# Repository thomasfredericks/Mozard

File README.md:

# Mozard

Mozard is a miniature, open-source digital synthesizer based on the Mozzi audio library and an Arduino Nano (ATmega328p) board.

[Video demonstration](https://youtu.be/wlpf26ogcaQ)

Features :

- 12 capacitive touch pads (one full octave)
- 6 different sound algorithms
- MIDI input support
- Octave control via potentiometer
- Volume control via potentiometer
- Built-in arpeggiator
- Decay and arpeggiator speed control

## Usage

The Mozard changes behavior when the arpeggiator is deactivated or activated. When in arpeggiator mode, the LED on the Arduino blinks in sync with the arpeggiator interval.

## Hardware

The circuit and Bill Of Materials can be found in the extras/circuit folder.

## Source code

1) Download the library source code [here](https://github.com/thomasfredericks/Mozard/archive/refs/heads/master.zip).

2) Extract into your Arduino libraries folder. It should look something like this:

3) Open Arduino.

4) Find the latest example:

5) Configure Arduino for the right microcontroller i.e. "Arduino Nano":

7) Configure Arduino for the right Bootloader i.e. "ATmega328 (Old Bootloader)"  if you followed a Mozard workshop or bought a clone:

8) Compile and transfer.

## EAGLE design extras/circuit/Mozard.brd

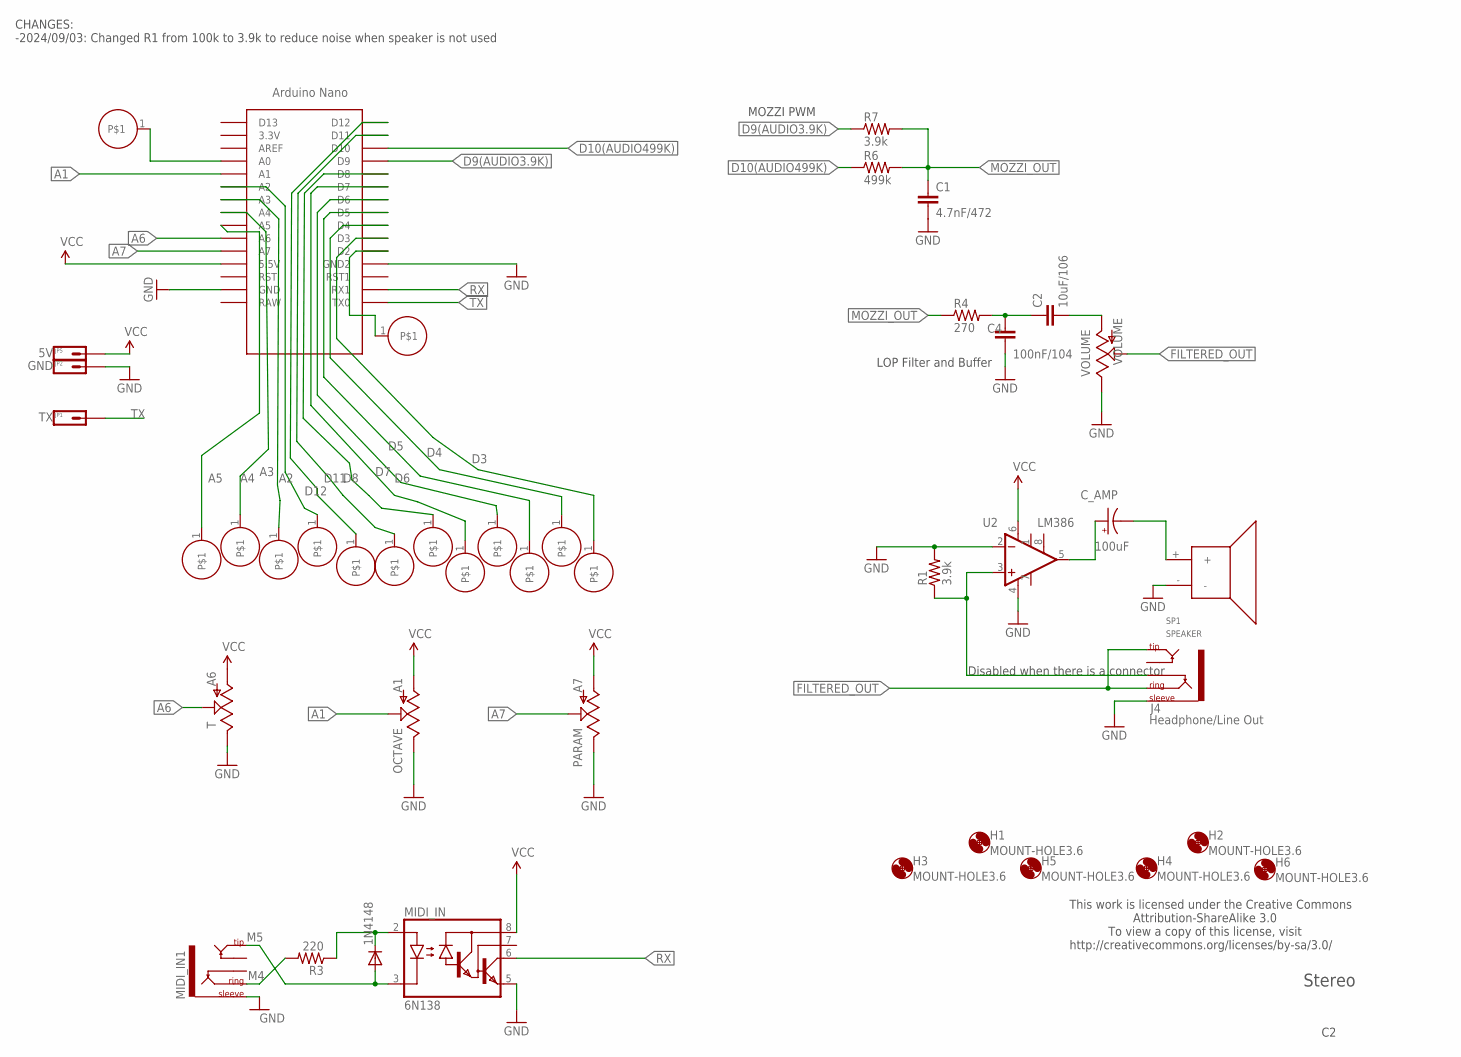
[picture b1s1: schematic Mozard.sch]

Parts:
1N4148: 1N4148; DO41-10
C1: 4.7nF/472; CAP-PTH-SMALL-KIT
C2: 10uF/106; CAP-PTH-SMALL-KIT
C4: 100nF/104; CAP-PTH-SMALL-KIT
C_AMP: 100uF; CPOL-RADIAL-10UF-25V
H1, H2, H3, H4, H5, H6: MOUNT-HOLE3.6; 3,6
J4: Headphone/Line Out; AUDIO-JACK
JP1: TX; 1X01_SIDE_NAME
JP2: GND; 1X01_SIDE_NAME
JP5: 5V; 1X01_SIDE_NAME
MIDI_IN: 6N138; DIL08
MIDI_IN1: AUDIO-JACKKIT; AUDIO-JACK-KIT
OCTAVE: A1; ALPS_POT
PARAM: A7; ALPS_POT
R1, R7: 3.9k; 0204/7
R3: 220; 0204/5
R4: 270; 0204/7
R6: 499k; 0204/7
SP1: SPEAKER; PCB_MOUNT_SPEAKER
T: A6; ALPS_POT
U2: LM386; DIP08
U$1: NANO
U$2, U$3, U$4, U$5, U$6, U$7, U$8, U$9, U$10, U$11, U$12, U$13, U$14, U$15: PCB-TOUCHPAD-1-PIN
VOLUME: VOLUME; ALPS_POT

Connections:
A1: OCTAVE.P$2 (S), U$1.A1
A2: U$1.A2, U$5.1
A3: U$1.A3, U$4.1
A4: U$1.A4, U$3.1
A5: U$1.A5, U$2.1
A6: T.P$2 (S), U$1.A6
A7: PARAM.P$2 (S), U$1.A7
D3: U$1.D3, U$13.1
D4: U$1.D4, U$12.1
D5: U$1.D5, U$11.1
D6: U$1.D6, U$10.1
D7: U$1.D7, U$9.1
D8: U$1.D8, U$8.1
D9(AUDIO3.9K): R7.1, U$1.D9
D10(AUDIO499K): R6.1, U$1.D10
D11: U$1.D11, U$7.1
D12: U$1.D12, U$6.1
FILTERED_OUT: J4.RING, J4.TIP, VOLUME.P$2 (S)
GND: C1.2, C4.2, J4.SLEEVE, JP2.1, MIDI_IN.5 (GND), MIDI_IN1.SLEEVE, OCTAVE.P$1 (E), PARAM.P$1 (E), R1.2, SP1.-, T.P$1 (E), U2.2 (-IN), U2.4 (V-), U$1.GND, U$1.GND1 (GND2), VOLUME.P$1 (E)
M4: MIDI_IN1.RING, R3.2
M5: 1N4148.A, MIDI_IN.3 (C), MIDI_IN1.TIP
MOZZI_OUT: C1.1, R4.1, R6.2, R7.2
unnamed: C_AMP.+, U2.5 (OUT)
unnamed: C2.2, VOLUME.P$3 (A)
unnamed: U$1.A0, U$15.1
unnamed: C2.1, C4.1, R4.2
unnamed: C_AMP.-, SP1.+
unnamed: J4.RSH, R1.1, U2.3 (+IN)
unnamed: 1N4148.C, MIDI_IN.2 (A), R3.1
RX: MIDI_IN.6 (VO), U$1.RX1
TOUCH_A: U$1.D2, U$14.1
TX: JP1.1, U$1.TX0
VCC: JP5.1, MIDI_IN.8 (VCC), OCTAVE.P$3 (A), PARAM.P$3 (A), T.P$3 (A), U2.6 (V+), U$1.5V (5.5V)

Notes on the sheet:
Stereo
Disabled when there is a connector
This work is licensed under the Creative Commons Attribution-ShareAlike 3.0 To view a copy of this license, visit http://creativecommons.org/licenses/by-sa/3.0/
LOP Filter and Buffer
MOZZI PWM
CHANGES: -2024/09/03: Changed R1 from 100k to 3.9k to reduce noise when speaker is not used

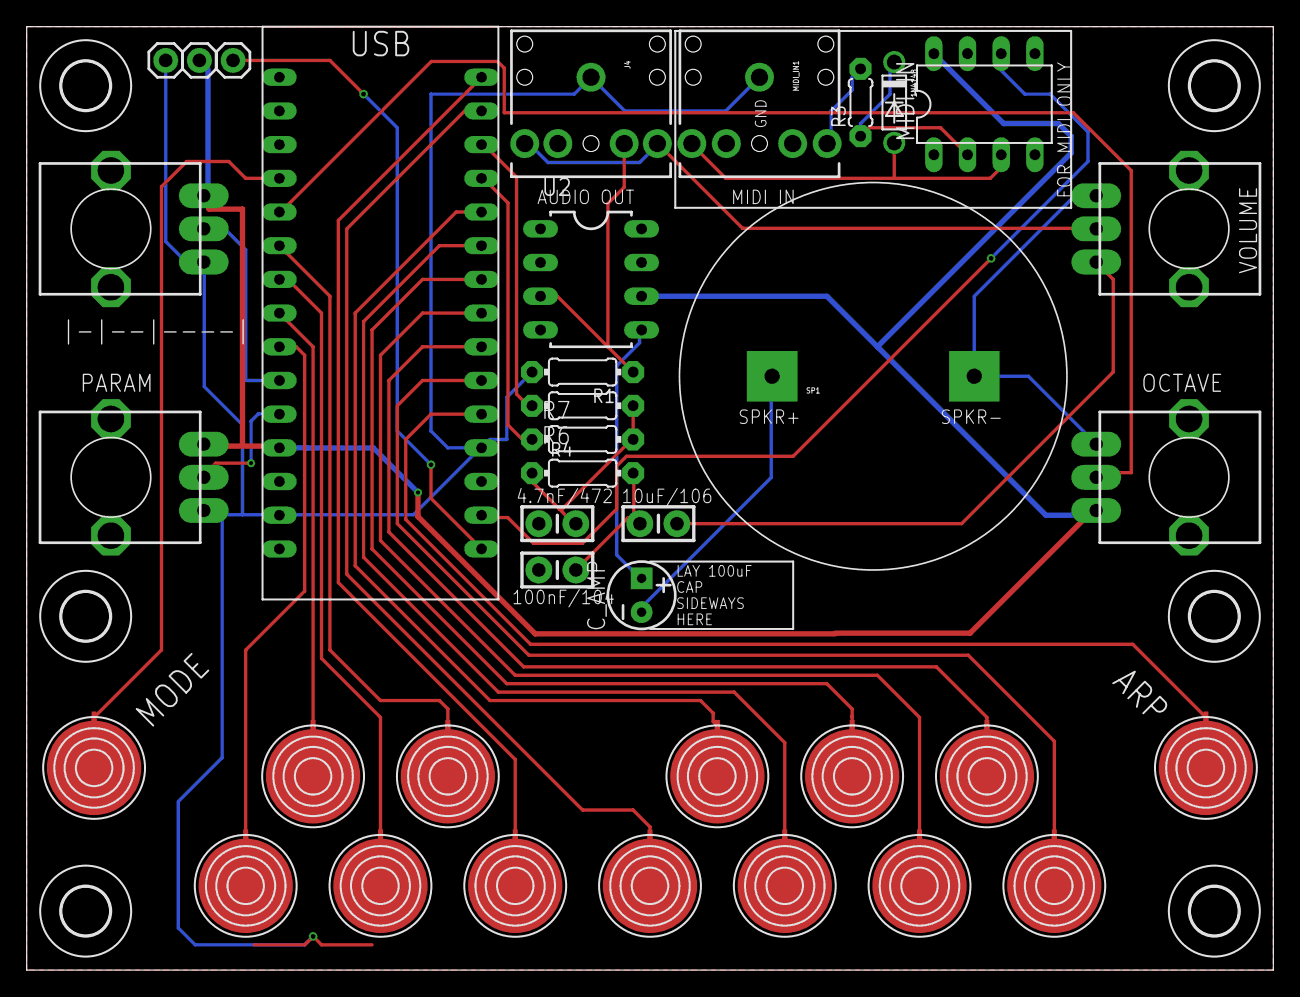
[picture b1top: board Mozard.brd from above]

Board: 2 copper layers, 94.0 x 71.1 mm, 43 parts (0 on the bottom side), 33 nets.

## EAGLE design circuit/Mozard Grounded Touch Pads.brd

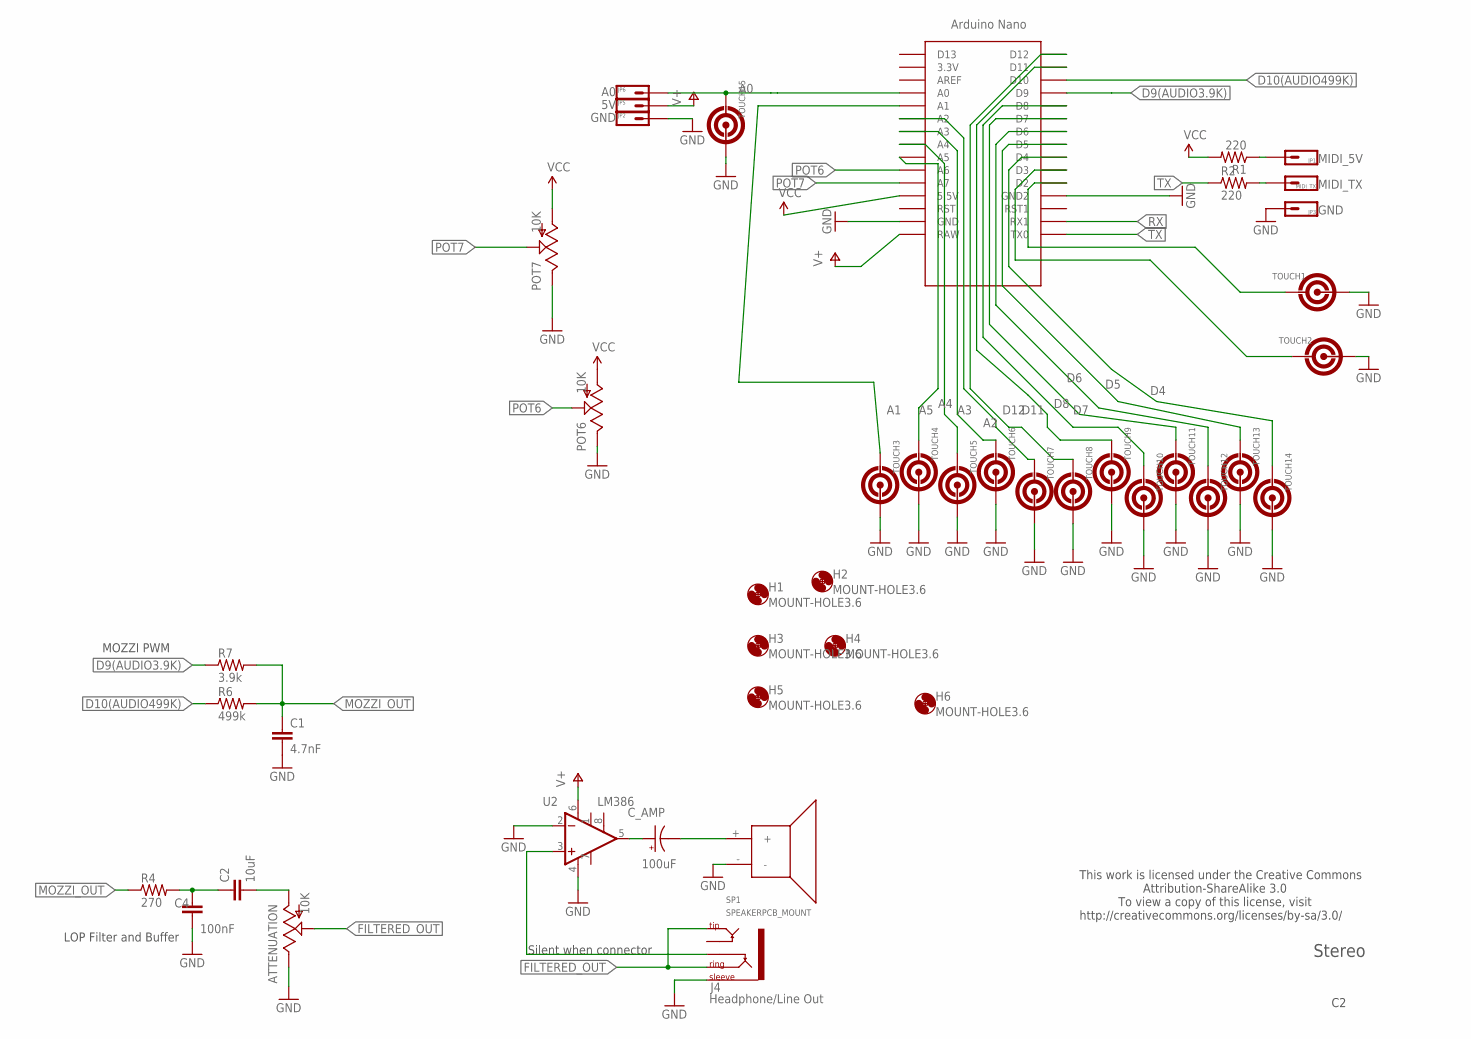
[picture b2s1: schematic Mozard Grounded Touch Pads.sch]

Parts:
ATTENUATION: 10K; ALPS_POT_KIT
C1: 4.7nF; CAP-PTH-SMALL-KIT
C2: 10uF; CAP-PTH-SMALL-KIT
C4: 100nF; CAP-PTH-SMALL-KIT
C_AMP: 100uF; CPOL-RADIAL-10UF-25V
H1, H2, H3, H4, H5, H6: MOUNT-HOLE3.6; 3,6
J4: Headphone/Line Out; AUDIO-JACK
JP1: MIDI_5V; 1X01_SIDE_NAME
JP2, JP3: GND; 1X01_SIDE_NAME
JP5: 5V; 1X01_SIDE_NAME
JP6: A0; 1X01_SIDE_NAME
MIDI_TX: MIDI_TX; 1X01_SIDE_NAME
POT6, POT7: 10K; ALPS_POT_KIT
R1, R2: 220; 0204/7
R4: 270; 0204/7
R6: 499k; 0204/7
R7: 3.9k; 0204/7
SP1: SPEAKERPCB_MOUNT; PCB_MOUNT_SPEAKER
TOUCH1, TOUCH2, TOUCH3, TOUCH4, TOUCH5, TOUCH6, TOUCH7, TOUCH8, TOUCH9, TOUCH10, TOUCH11, TOUCH12, TOUCH13, TOUCH14, TOUCH15: PCB-TOUCHPAD2
U2: LM386; DIP08
U$1: NANO

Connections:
A0: JP6.1, TOUCH15.1, U$1.A0
A1: TOUCH3.1, U$1.A1
A2: TOUCH7.1, U$1.A2
A3: TOUCH6.1, U$1.A3
A4: TOUCH5.1, U$1.A4
A5: TOUCH4.1, U$1.A5
D4: TOUCH14.1, U$1.D4
D5: TOUCH13.1, U$1.D5
D6: TOUCH12.1, U$1.D6
D7: TOUCH11.1, U$1.D7
D8: TOUCH10.1, U$1.D8
D9(AUDIO3.9K): R7.1, U$1.D9
D10(AUDIO499K): R6.1, U$1.D10
D11: TOUCH9.1, U$1.D11
D12: TOUCH8.1, U$1.D12
FILTERED_OUT: ATTENUATION.P$2 (S), J4.RING, J4.TIP
GND: ATTENUATION.P$1 (E), C1.2, C4.2, J4.SLEEVE, JP2.1, JP3.1, POT6.P$1 (E), POT7.P$1 (E), SP1.-, TOUCH1.2, TOUCH2.2, TOUCH3.2, TOUCH4.2, TOUCH5.2, TOUCH6.2, TOUCH7.2, TOUCH8.2, TOUCH9.2, TOUCH10.2, TOUCH11.2, TOUCH12.2, TOUCH13.2, TOUCH14.2, TOUCH15.2, U2.2 (-IN), U2.4 (V-), U$1.GND, U$1.GND1 (GND2)
MOZZI_OUT: C1.1, R4.1, R6.2, R7.2
unnamed: C_AMP.-, SP1.+
unnamed: ATTENUATION.P$3 (A), C2.2
unnamed: JP1.1, R1.1
unnamed: C2.1, C4.1, R4.2
unnamed: MIDI_TX.1, R2.2
unnamed: J4.RSH, U2.3 (+IN)
unnamed: C_AMP.+, U2.5 (OUT)
POT6: POT6.P$2 (S), U$1.A6
POT7: POT7.P$2 (S), U$1.A7
RX: U$1.RX1
TOUCH_A: TOUCH1.1, U$1.D2
TOUCH_B: TOUCH2.1, U$1.D3
TX: R2.1, U$1.TX0
V+: JP5.1, U2.6 (V+), U$1.RAW
VCC: POT6.P$3 (A), POT7.P$3 (A), R1.2, U$1.5V (5.5V)

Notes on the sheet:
Stereo
Silent when connector
This work is licensed under the Creative Commons Attribution-ShareAlike 3.0 To view a copy of this license, visit http://creativecommons.org/licenses/by-sa/3.0/
LOP Filter and Buffer
MOZZI PWM

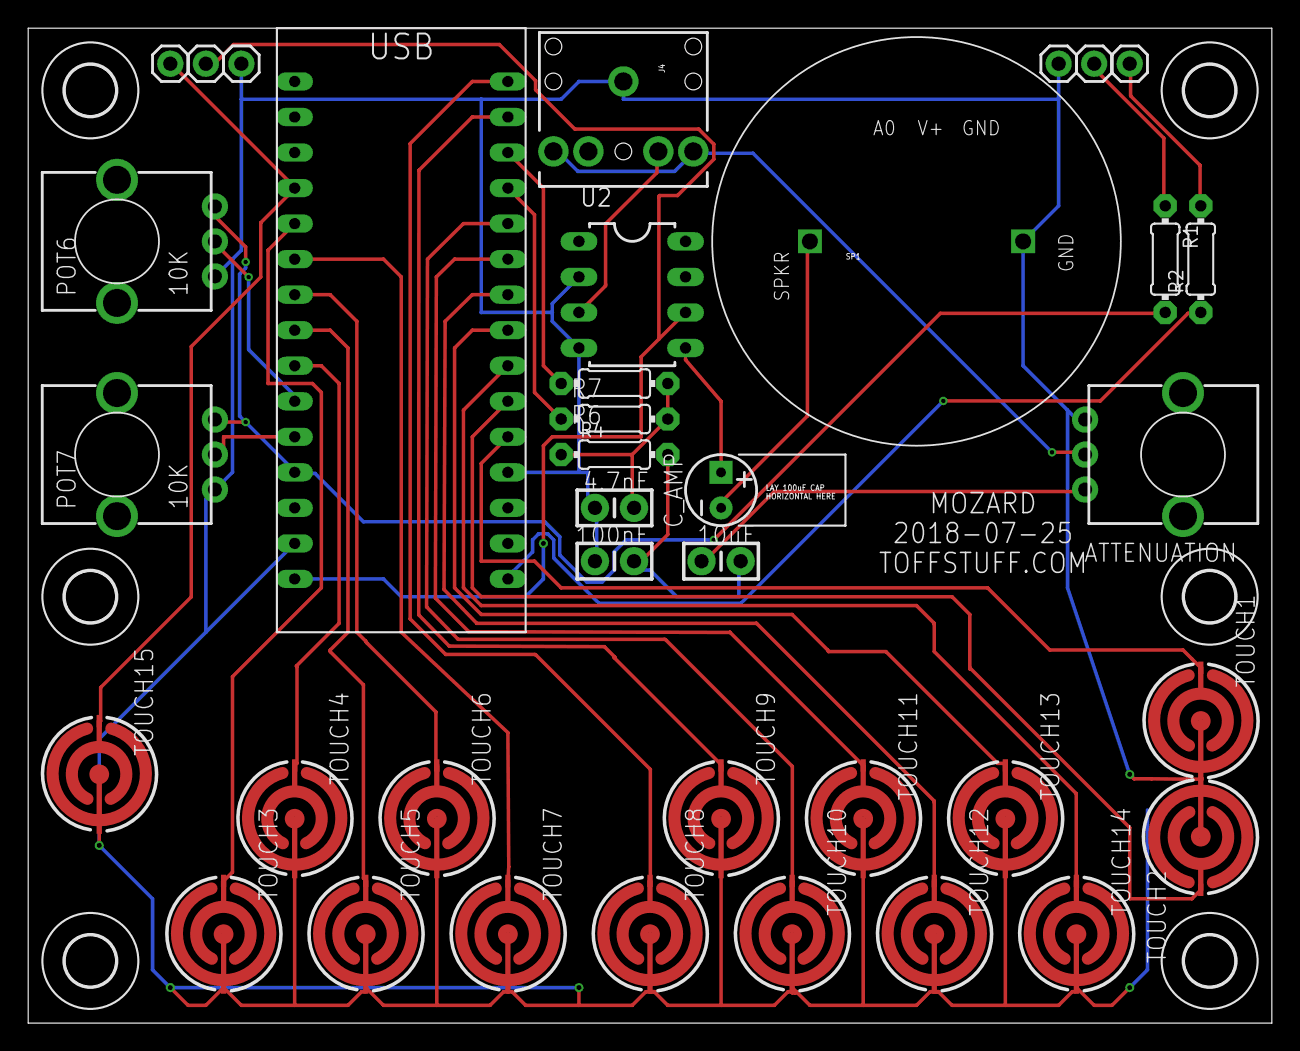
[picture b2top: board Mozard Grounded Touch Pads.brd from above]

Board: 2 copper layers, 88.9 x 71.1 mm, 43 parts (0 on the bottom side), 32 nets.

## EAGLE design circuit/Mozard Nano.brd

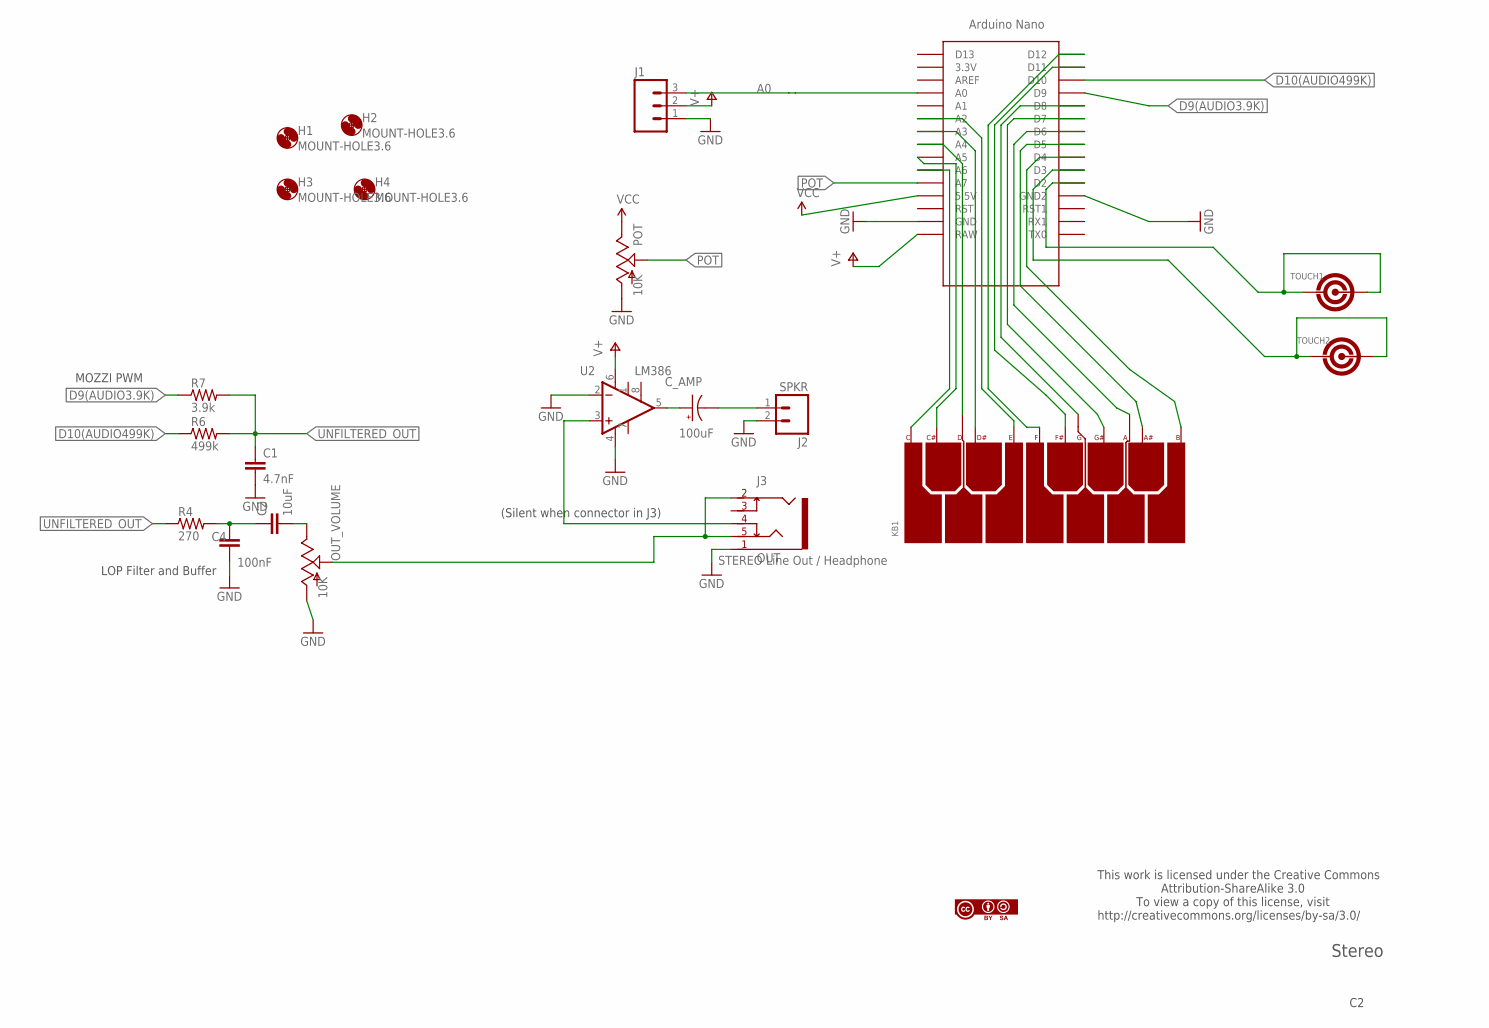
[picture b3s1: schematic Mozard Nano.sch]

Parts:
C1: 4.7nF; CAP-PTH-SMALL-KIT
C2: 10uF; CAP-PTH-SMALL-KIT
C4: 100nF; CAP-PTH-SMALL-KIT
C_AMP: 100uF; CPOL-RADIAL-10UF-25V
H1, H2, H3, H4: MOUNT-HOLE3.6; 3,6
J1: M03SCREW; SCREWTERMINAL-3.5MM-3
J2: SPKR; SCREWTERMINAL-3.5MM-2
J3: OUT; STEREO-AUDIO-3.5MM-SWITCHED
KB1: PCB-KEYBOARD4
OUT_VOLUME: 10K; ALPS_POT_KIT
POT: 10K; ALPS_POT_KIT
R4: 270; 0204/5
R6: 499k; 0204/5
R7: 3.9k; 0204/5
TOUCH1, TOUCH2: PCB-TOUCHPAD2
U2: LM386; DIP08
U$1: NANO
U$2: CC-BY-SA-LOGO2

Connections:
A0: J1.3, U$1.A0
D2(C): KB1.D#, U$1.A3
D9(AUDIO3.9K): R7.1, U$1.D9
D10(AUDIO499K): R6.1, U$1.D10
GND: C1.2, C4.2, J1.1, J2.2, J3.1, OUT_VOLUME.P$3 (A), POT.P$3 (A), U2.2 (-IN), U2.4 (V-), U$1.GND, U$1.GND1 (GND2)
unnamed: C_AMP.-, J2.1
unnamed: KB1.E, U$1.A2
unnamed: KB1.C, U$1.A6
unnamed: C2.1, C4.1, R4.2
unnamed: C2.2, OUT_VOLUME.P$1 (E)
unnamed: J3.4, U2.3 (+IN)
unnamed: C_AMP.+, U2.5 (OUT)
unnamed: J3.2, J3.5, OUT_VOLUME.P$2 (S)
unnamed: KB1.C#, U$1.A5
unnamed: KB1.D, U$1.A4
unnamed: KB1.F, U$1.D12
unnamed: KB1.F#, U$1.D11
unnamed: KB1.G, U$1.D8
unnamed: KB1.G#, U$1.D7
unnamed: KB1.A, U$1.D6
unnamed: KB1.A#, U$1.D5
unnamed: KB1.B, U$1.D4
POT: POT.P$2 (S), U$1.A7
TOUCH_A: TOUCH1.1, TOUCH1.2, U$1.D2
TOUCH_B: TOUCH2.1, TOUCH2.2, U$1.D3
UNFILTERED_OUT: C1.1, R4.1, R6.2, R7.2
V+: J1.2, U2.6 (V+), U$1.RAW
VCC: POT.P$1 (E), U$1.5V (5.5V)

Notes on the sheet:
Stereo
STEREO Line Out / Headphone
(Silent when connector in J3)
This work is licensed under the Creative Commons Attribution-ShareAlike 3.0 To view a copy of this license, visit http://creativecommons.org/licenses/by-sa/3.0/
LOP Filter and Buffer
MOZZI PWM

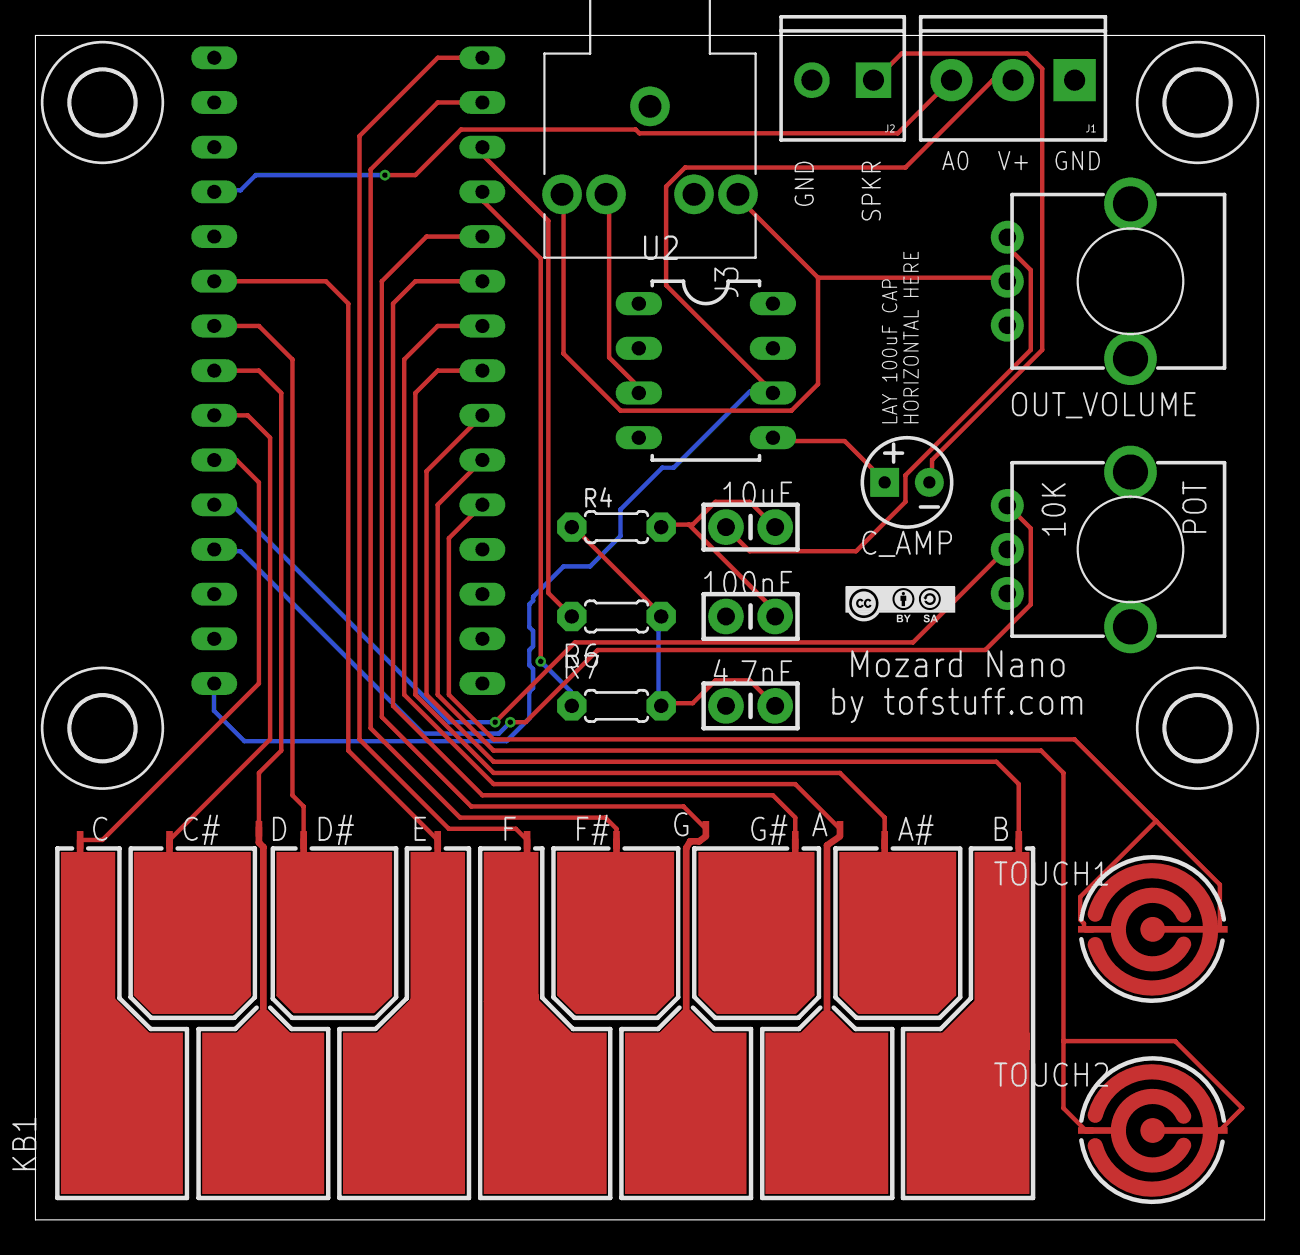
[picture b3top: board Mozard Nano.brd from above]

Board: 2 copper layers, 69.8 x 67.3 mm, 22 parts (0 on the bottom side), 28 nets.

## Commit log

2016-04-28 USBaspLoader for Mozart (atmega328p)
2018-05-04 Updating
2018-05-04 Readme
2018-05-20 Fixes and added other potentiometer
2018-05-22 Separating prototype from final version
2018-05-22 Clean-up
2018-07-25 Mozard Nano Prototype Release
2018-07-25 Version 1.00
2018-07-25 New version with grounded touch pads
2018-07-27 Adding examples
2018-07-27 Version sub directory
2018-09-12 integrated Mozzi
2018-09-12 Now compliles
2018-09-12 Added circuit
2018-09-13 Updated code and example
2018-09-13 Fixed Arpeggiator
2018-09-13 Fixed octave issue
2018-09-24 Removed CONTROL_RATE warning
2019-02-16 Fixed overlapping traces
2019-07-31 Sensitivity change
2019-08-29 Cap removed, resistor added
    Big capacitor removed because it was useless. 100k resistor added between + and - of amp to cancel noise when jack plugged in.
2019-09-10 Removed a debug print
2019-09-10 Added MIDI
2019-11-07 New board + poly
2019-11-07 Clean up
2019-11-08 Updated the code
2019-11-12 Cleaned everything and it all works nice
2019-12-05 Added serial control example and updated MIDI input
2019-12-05 New example
2020-01-16 Added ADSR
2020-12-08 New version
2022-01-25 Updated BOM
2024-08-23 Changed MIDI code
2024-08-24 Added a picture
2024-09-04 Updated Arp behavior
2024-09-04 More doc
2024-09-04 Added medias folder
2024-09-04 Documentation
2024-09-04 Reactivated the hidden modes

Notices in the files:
parts and their libraries:
SparkFun-Electromechanical: Licensing: Creative Commons ShareAlike 4.0 International - https://creativecommons.org/licenses/by-sa/4.0
